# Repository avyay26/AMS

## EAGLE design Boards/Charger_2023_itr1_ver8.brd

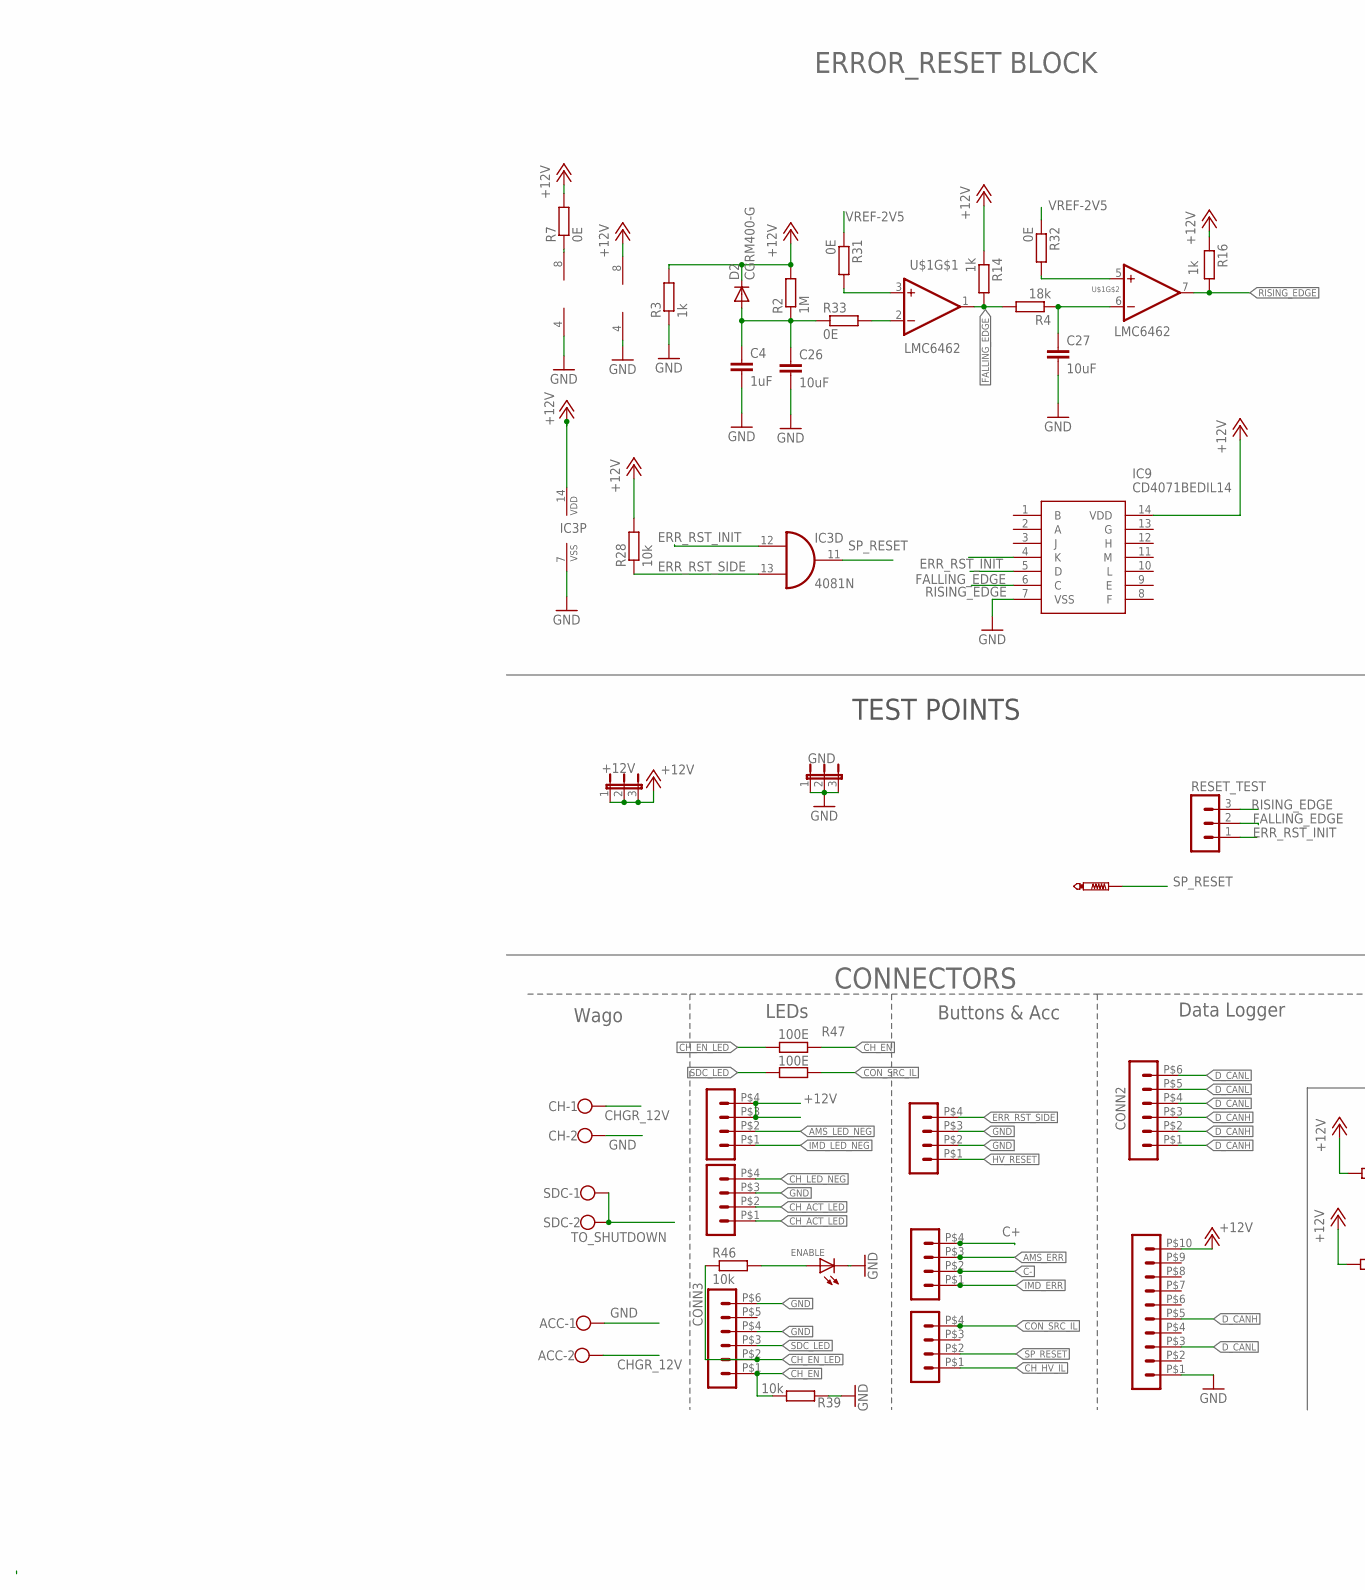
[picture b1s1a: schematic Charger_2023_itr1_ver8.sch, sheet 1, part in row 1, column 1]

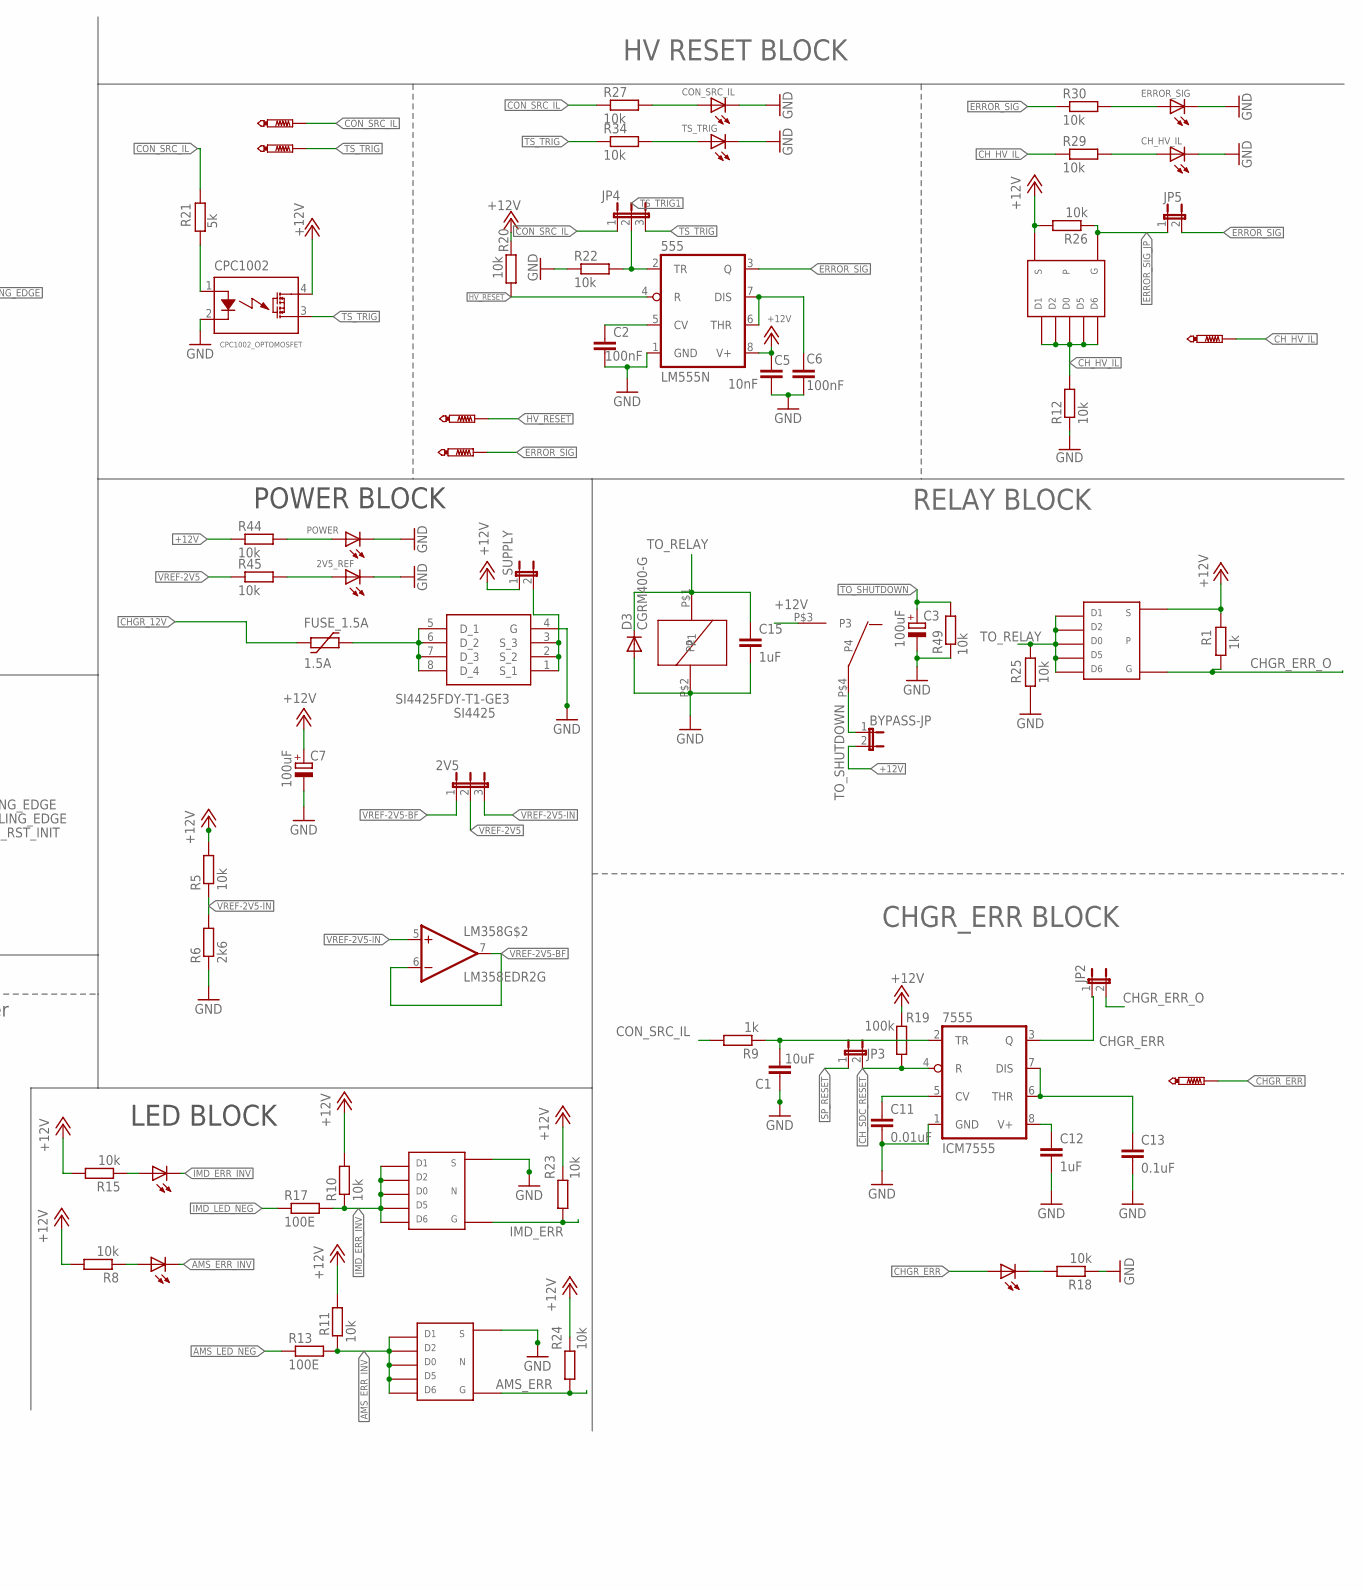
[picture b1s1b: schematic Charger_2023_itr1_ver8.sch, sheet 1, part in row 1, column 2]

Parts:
2V5: JP2E; JP2
2V5_REF: LED-FKIT-1206; FKIT-LED-1206
555: LM555N; DIL08
7555: ICM7555; DIL08
+12V: JP2E; JP2
ACC: W237-102
ACU, ACU1, ACU2, ACU3, ACU4: HEADER_POS4_43045-0412; 43045-0412
AMS: LED-FKIT-1206; FKIT-LED-1206
BYPASS-JP: JP1E; JP1
C1, C26, C27: 10uF; C0805
C2, C6: 100nF; C0805
C3, C7: 100uF; E2,5-6
C4, C12, C15: 1uF; C0805
C5: 10nF; C0805
C11: 0.01uF; C0805
C13: 0.1uF; C0805
CH: W237-102
CH-HV-IL: PTR1PAD1-13; P1-13
CHGR-ERR: PTR1PAD1-13; P1-13
CHGR_ERR: LED-FKIT-1206; FKIT-LED-1206
CH_HV_IL: LED-FKIT-1206; FKIT-LED-1206
CON-SRC-IL: PTR1PAD1-13; P1-13
CONN2, CONN3: HEADER_POS6_43045-0612; 43045-0612
CON_SRC_IL: LED-FKIT-1206; FKIT-LED-1206
CPC1002: CPC1002_OPTOMOSFET; SOP04
D2, D3: CGRM400-G; SOD-123_MINI-SMA
ENABLE: LED-FKIT-1206; FKIT-LED-1206
ERROR-SIG: PTR1PAD1-13; P1-13
ERROR_SIG: LED-FKIT-1206; FKIT-LED-1206
FUSE_1.5A: 1.5A; 1206L
GND: JP2E; JP2
HV-RESET: PTR1PAD1-13; P1-13
IC3: 4081N; DIL14
IC9: CD4071BEDIL14; DIL14
IMD: LED-FKIT-1206; FKIT-LED-1206
JP2, JP3, JP5: JP1E; JP1
JP4: JP2E; JP2
LM358: LM358EDR2G; SOIC-8
POWER: LED-FKIT-1206; FKIT-LED-1206
R1, R3, R9, R14, R16: 1k; R0805
R2: 1M; R0805
R4: 18k; R0805
R5, R8, R10, R11, R12, R15, R18, R20, R22, R23, R24, R25, R26, R27, R28, R29, R30, R34, R39, R44, R45, R46, R49: 10k; R0805
R6: 2k6; R0805
R7, R31, R32, R33: 0E; R0805
R13, R17: 100E; M0805
R19: 100k; R0805
R21: 5k; R0805
R47, R48: 100E; R0805
RESET_TEST: MA03-1
SDC: W237-102
SI4425: SI4425FDY-T1-GE3; SOIC127P600X175-8N
SP_RESET: PTR1PAD1-13; P1-13
SUPPLY: JP1E; JP1
TS-TRIG: PTR1PAD1-13; P1-13
TS_TRIG: LED-FKIT-1206; FKIT-LED-1206
U$1: LMC6462; S08
U$3, U$8: TSOP-6_PMOS
U$5, U$7: TSOP-6_NMOS
U$9: G6DN_RELAY
X5: HEADER_POS10_43045-1012; 43045-1012

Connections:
+12V: 555.8 (V+), 7555.8 (V+), +12V.1, +12V.2, +12V.3, ACU.P$3 (3), ACU.P$4 (4), BYPASS-JP.2, C5.1, C7.+, C12.1, CPC1002.4, D2.C, IC3.14 (VDD), IC9.14 (VDD), LM358.8 (V+), R1.2, R2.2, R3.2, R5.2, R7.2, R8.2, R10.2, R11.2, R14.1, R15.2, R16.1, R19.1, R20.2, R23.2, R24.2, R26.2, R28.2, R44.1, SUPPLY.1, U$3.S, U$8.S, U$9.P$3 (P3), X5.P$10 (10); also elsewhere on the board
AMS_ERR: ACU3.P$3 (3), R24.1, U$5.G
AMS_ERR_INV: AMS.C, R11.1, R13.2, U$5.1, U$5.2, U$5.5, U$5.6, U$5.D (D0)
AMS_LED_NEG: ACU.P$2 (2), R13.1
C+: ACU3.P$4 (4); also elsewhere on the board
C-: ACU3.P$2 (2); also elsewhere on the board
CHGR_12V: ACC.2, CH.1, FUSE_1.5A.P$1 (1)
CHGR_ERR: 7555.3 (Q), CHGR-ERR.TP, CHGR_ERR.A, JP2.1
CHGR_ERR_O: JP2.2, R1.1, U$3.G
CH_ACT_LED: ACU2.P$1 (1), ACU2.P$2 (2); also elsewhere on the board
CH_EN: CONN3.P$1 (1), R39.2, R47.2
CH_EN_LED: CONN3.P$2 (2), R46.1, R47.1
CH_HV_IL: ACU4.P$1 (1), CH-HV-IL.TP, R12.2, R29.1, U$8.1, U$8.2, U$8.5, U$8.6, U$8.D (D0)
CH_LED_NEG: ACU2.P$4 (4); also elsewhere on the board
CH_SDC_RESET: 7555.4 (R), JP3.2, R19.2
CON_SRC_IL: ACU4.P$4 (4), CON-SRC-IL.TP, JP4.1, R9.2, R21.2, R27.1, R48.2
D_CANH: CONN2.P$1 (1), CONN2.P$2 (2), CONN2.P$3 (3), X5.P$5 (5)
D_CANL: CONN2.P$4 (4), CONN2.P$5 (5), CONN2.P$6 (6), X5.P$3 (3)
ERROR_SIG: 555.3 (Q), ERROR-SIG.TP, JP5.2, R30.1
ERROR_SIG_JP: JP5.1, R26.1, U$8.G
ERR_RST_INIT: IC3.12 (I0), IC9.4 (K), RESET_TEST.1
ERR_RST_SIDE: ACU1.P$4 (4), IC3.13 (I1), R28.1
FALLING_EDGE: IC9.5 (D), R4.2, R14.2, RESET_TEST.2, U$1.1 (OUT)
GND: 2V5_REF.C, 555.1 (GND), 7555.1 (GND), ACC.1, ACU1.P$2 (2), ACU1.P$3 (3), ACU2.P$3 (3), C1.1, C2.2, C3.-, C4.2, C5.2, C6.2, C7.-, C11.2, C12.2, C13.2, C15.2, C26.2, C27.2, CH.2, CH_HV_IL.C, CONN3.P$4 (4), CONN3.P$6 (6), CON_SRC_IL.C, CPC1002.2, D3.A, ENABLE.C, ERROR_SIG.C, GND.1, GND.2, GND.3, IC3.7 (VSS), IC9.7 (VSS), LM358.4 (V-), POWER.C, R3.1, R6.1, R12.1, R18.1, R22.1, R25.1, R39.1, R49.1, SI4425.4 (G), TS_TRIG.C, U$1.4 (V-), U$5.S, U$7.S, U$9.P$2 (P2), X5.P$1 (1); also elsewhere on the board
HV_RESET: 555.4 (R), ACU1.P$1 (1), HV-RESET.TP, R20.1
IMD_ERR: ACU3.P$1 (1), R23.1, U$7.G
IMD_ERR_INV: IMD.C, R10.1, R17.2, U$7.1, U$7.2, U$7.5, U$7.6, U$7.D (D0)
IMD_LED_NEG: ACU.P$1 (1), R17.1
unnamed: 7555.2 (TR), C1.2, R9.1
unnamed: IMD.A, R15.1
unnamed: 555.5 (CV), C2.1
unnamed: CHGR_ERR.C, R18.2
unnamed: R7.1, U$1.8 (V+)
unnamed: C4.1, C26.1, D2.A, R2.1, R33.1
unnamed: 555.6 (THR), 555.7 (DIS), C6.1
unnamed: AMS.A, R8.1
unnamed: CPC1002.1, R21.1
unnamed: CON_SRC_IL.A, R27.2
unnamed: CH_HV_IL.A, R29.2
unnamed: C27.1, R4.1, U$1.6 (-IN)
unnamed: ERROR_SIG.A, R30.2
unnamed: R34.2, TS_TRIG.A
unnamed: 7555.5 (CV), C11.1
unnamed: 7555.6 (THR), 7555.7 (DIS), C13.1
unnamed: SI4425.1 (S_1), SI4425.2 (S_2), SI4425.3 (S_3), SUPPLY.2
unnamed: FUSE_1.5A.P$2 (2), SI4425.5 (D_1), SI4425.6 (D_2), SI4425.7 (D_3), SI4425.8 (D_4)
unnamed: POWER.A, R44.2
unnamed: 2V5_REF.A, R45.2
unnamed: ENABLE.A, R46.2
unnamed: R31.2, U$1.3 (+IN)
unnamed: R32.2, U$1.5 (+IN)
unnamed: R33.2, U$1.2 (-IN)
RISING_EDGE: IC9.6 (C), R16.2, RESET_TEST.3, U$1.7 (OUT)
SDC_LED: CONN3.P$3 (3), R48.1
SP_RESET: ACU4.P$2 (2), IC3.11 (O), JP3.1, SP_RESET.TP
TO_RELAY: C15.1, D3.C, R25.2, U$3.1, U$3.2, U$3.5, U$3.6, U$3.D (D0), U$9.P$1 (P1)
TO_SHUTDOWN: BYPASS-JP.1, C3.+, R49.2, SDC.1, SDC.2, U$9.P$4 (P4)
TS_TRIG: CPC1002.3, JP4.3, R34.1, TS-TRIG.TP
TS_TRIG1: 555.2 (TR), JP4.2, R22.2
VREF-2V5: 2V5.2, R31.1, R32.1, R45.1
VREF-2V5-BF: 2V5.1, LM358.6 (-IN), LM358.7 (OUT)
VREF-2V5-IN: 2V5.3, LM358.5 (+IN), R5.1, R6.2

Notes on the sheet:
CHGR_ERR BLOCK
ERROR_RESET BLOCK
RELAY BLOCK
CONNECTORS
POWER BLOCK
TEST POINTS
LED BLOCK
HV RESET BLOCK
Wago
LEDs
Buttons & Acc
Data Logger

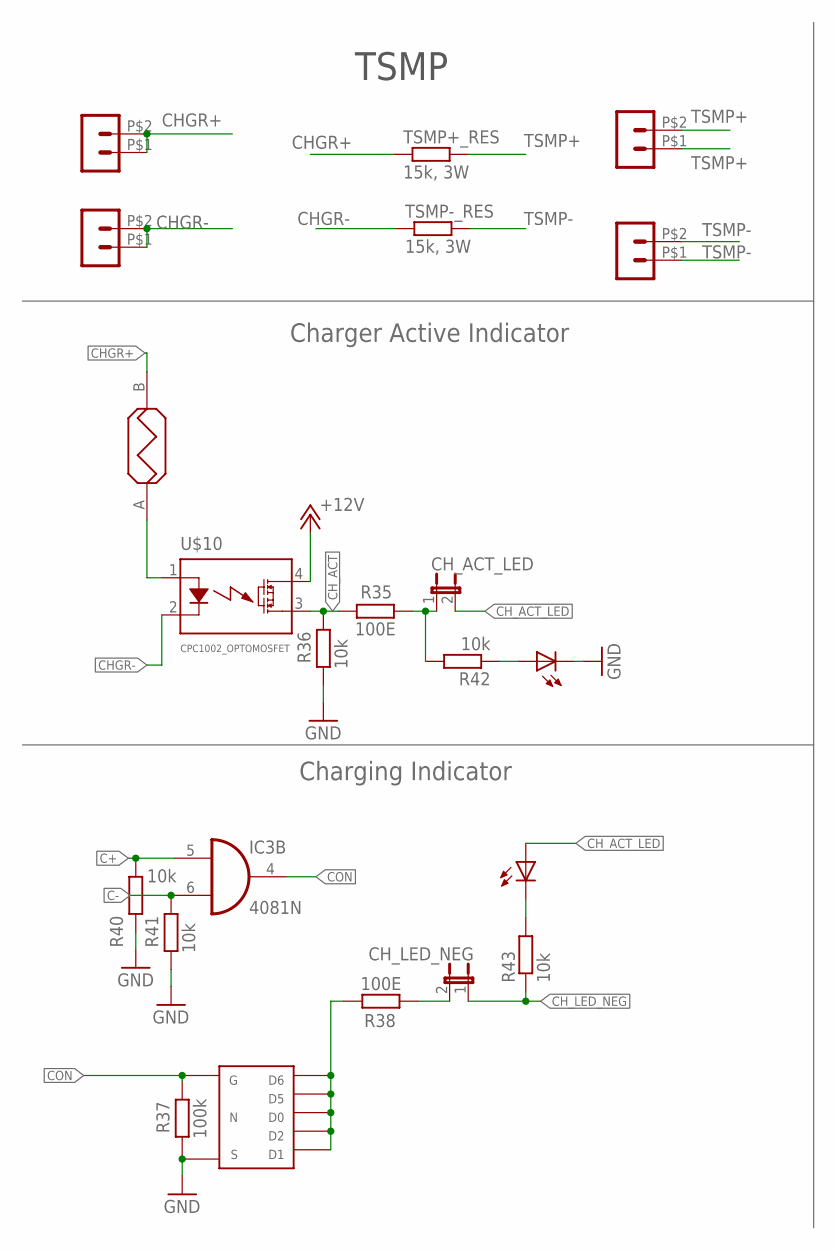
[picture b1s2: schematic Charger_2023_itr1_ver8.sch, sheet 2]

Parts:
CHARGING: LED-FKIT-1206; FKIT-LED-1206
CH_ACT: LED-FKIT-1206; FKIT-LED-1206
CH_ACT_LED: JP1E; JP1
CH_LED_NEG: JP1E; JP1
IC3: 4081N; DIL14
LV_ECU, LV_ECU1, LV_ECU2, LV_ECU3: HEADER_POS2_43045-0212; 43045-0212
R35, R38: 100E; M0805
R36, R40, R41: 10k; M0805
R37: 100k; M0805
R42, R43: 10k; R0805
TSMP+_RES: 15k, 3W; P0613/15
TSMP-_RES: 15k, 3W; P0613/15
U$2_100K10W2: POWER_RESISTOR
U$10: CPC1002_OPTOMOSFET; SOP04
U$12: TSOP-6_NMOS

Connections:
+12V: U$10.4; also elsewhere on the board
C+: IC3.5 (I0), R40.2; also elsewhere on the board
C-: IC3.6 (I1), R41.2; also elsewhere on the board
CHGR+: LV_ECU2.P$1 (1), LV_ECU2.P$2 (2), TSMP+_RES.1, U$2_100K10W2.B
CHGR-: LV_ECU3.P$1 (1), LV_ECU3.P$2 (2), TSMP-_RES.1, U$10.2
CH_ACT: R35.1, R36.2, U$10.3
CH_ACT_LED: CHARGING.A, CH_ACT_LED.2; also elsewhere on the board
CH_LED_NEG: CH_LED_NEG.1, R43.1; also elsewhere on the board
CON: IC3.4 (O), R37.2, U$12.G
GND: CH_ACT.C, R36.1, R37.1, R40.1, R41.1, U$12.S; also elsewhere on the board
unnamed: CH_ACT.A, R42.1
unnamed: R38.2, U$12.1, U$12.2, U$12.5, U$12.6, U$12.D (D0)
unnamed: CH_LED_NEG.2, R38.1
unnamed: CH_ACT_LED.1, R35.2, R42.2
unnamed: U$2_100K10W2.A, U$10.1
unnamed: CHARGING.C, R43.2
TSMP+: LV_ECU.P$1 (1), LV_ECU.P$2 (2), TSMP+_RES.2
TSMP-: LV_ECU1.P$1 (1), LV_ECU1.P$2 (2), TSMP-_RES.2

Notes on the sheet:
TSMP
Charger Active Indicator
Charging Indicator

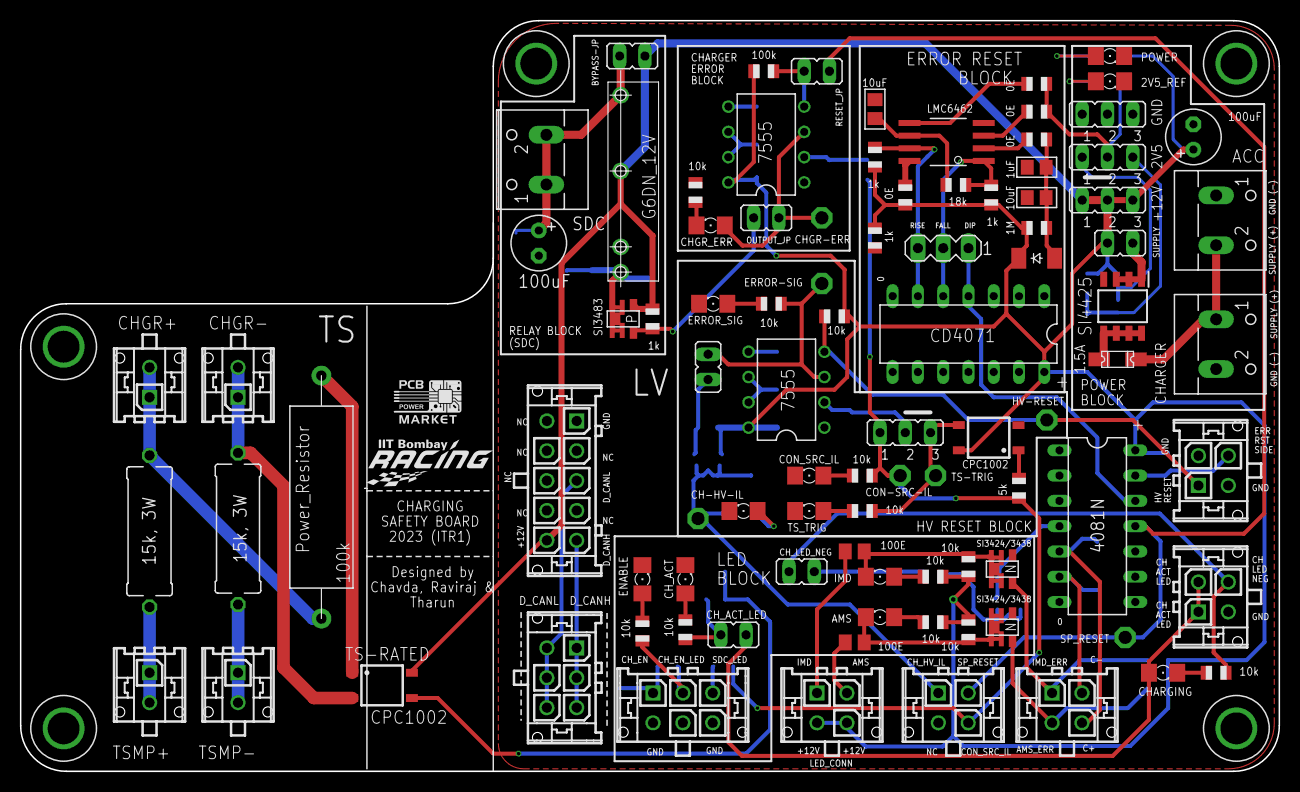
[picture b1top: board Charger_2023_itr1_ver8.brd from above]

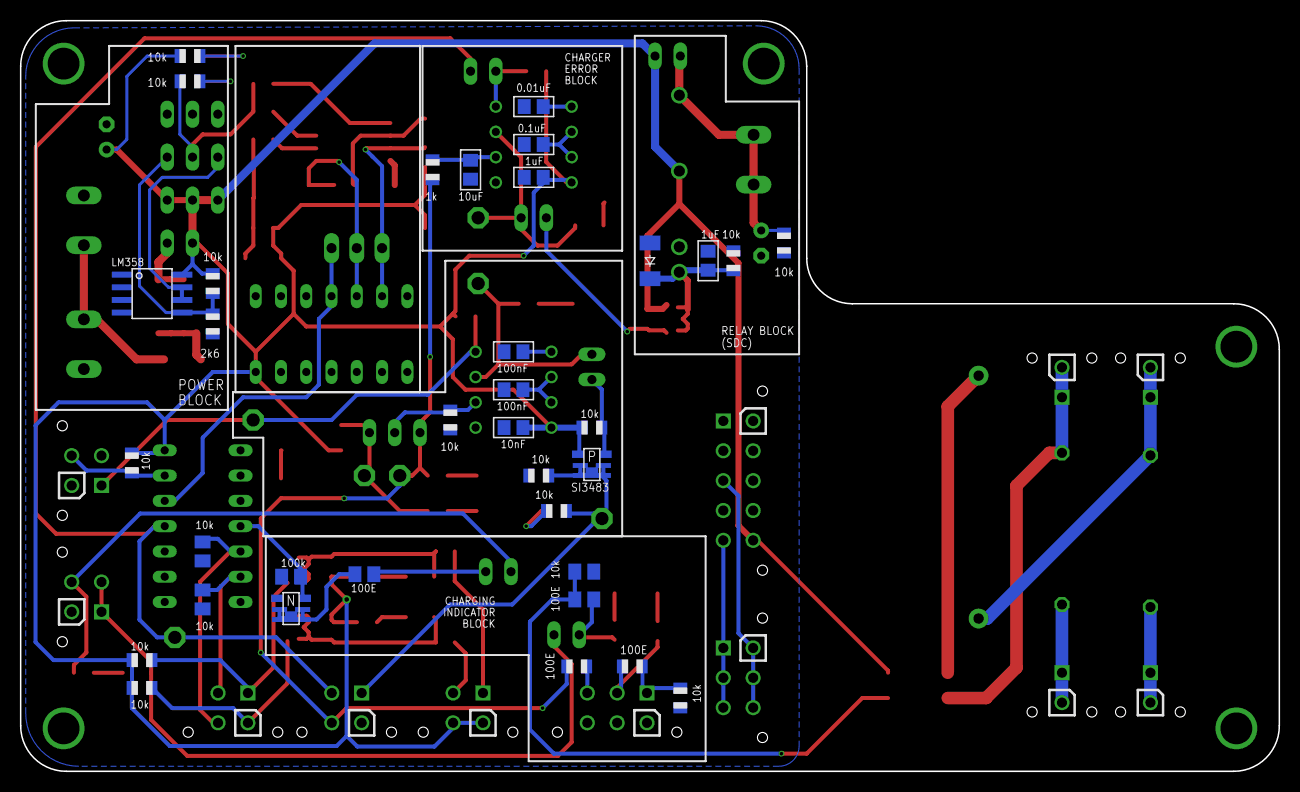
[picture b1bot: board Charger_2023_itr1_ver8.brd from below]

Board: 2 copper layers, 126.5 x 75.4 mm, 131 parts (35 on the bottom side), 74 nets.

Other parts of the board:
U$2: LOGO_PCBPOWER; 270X170
U$4: RACING_LOGO_190MIL

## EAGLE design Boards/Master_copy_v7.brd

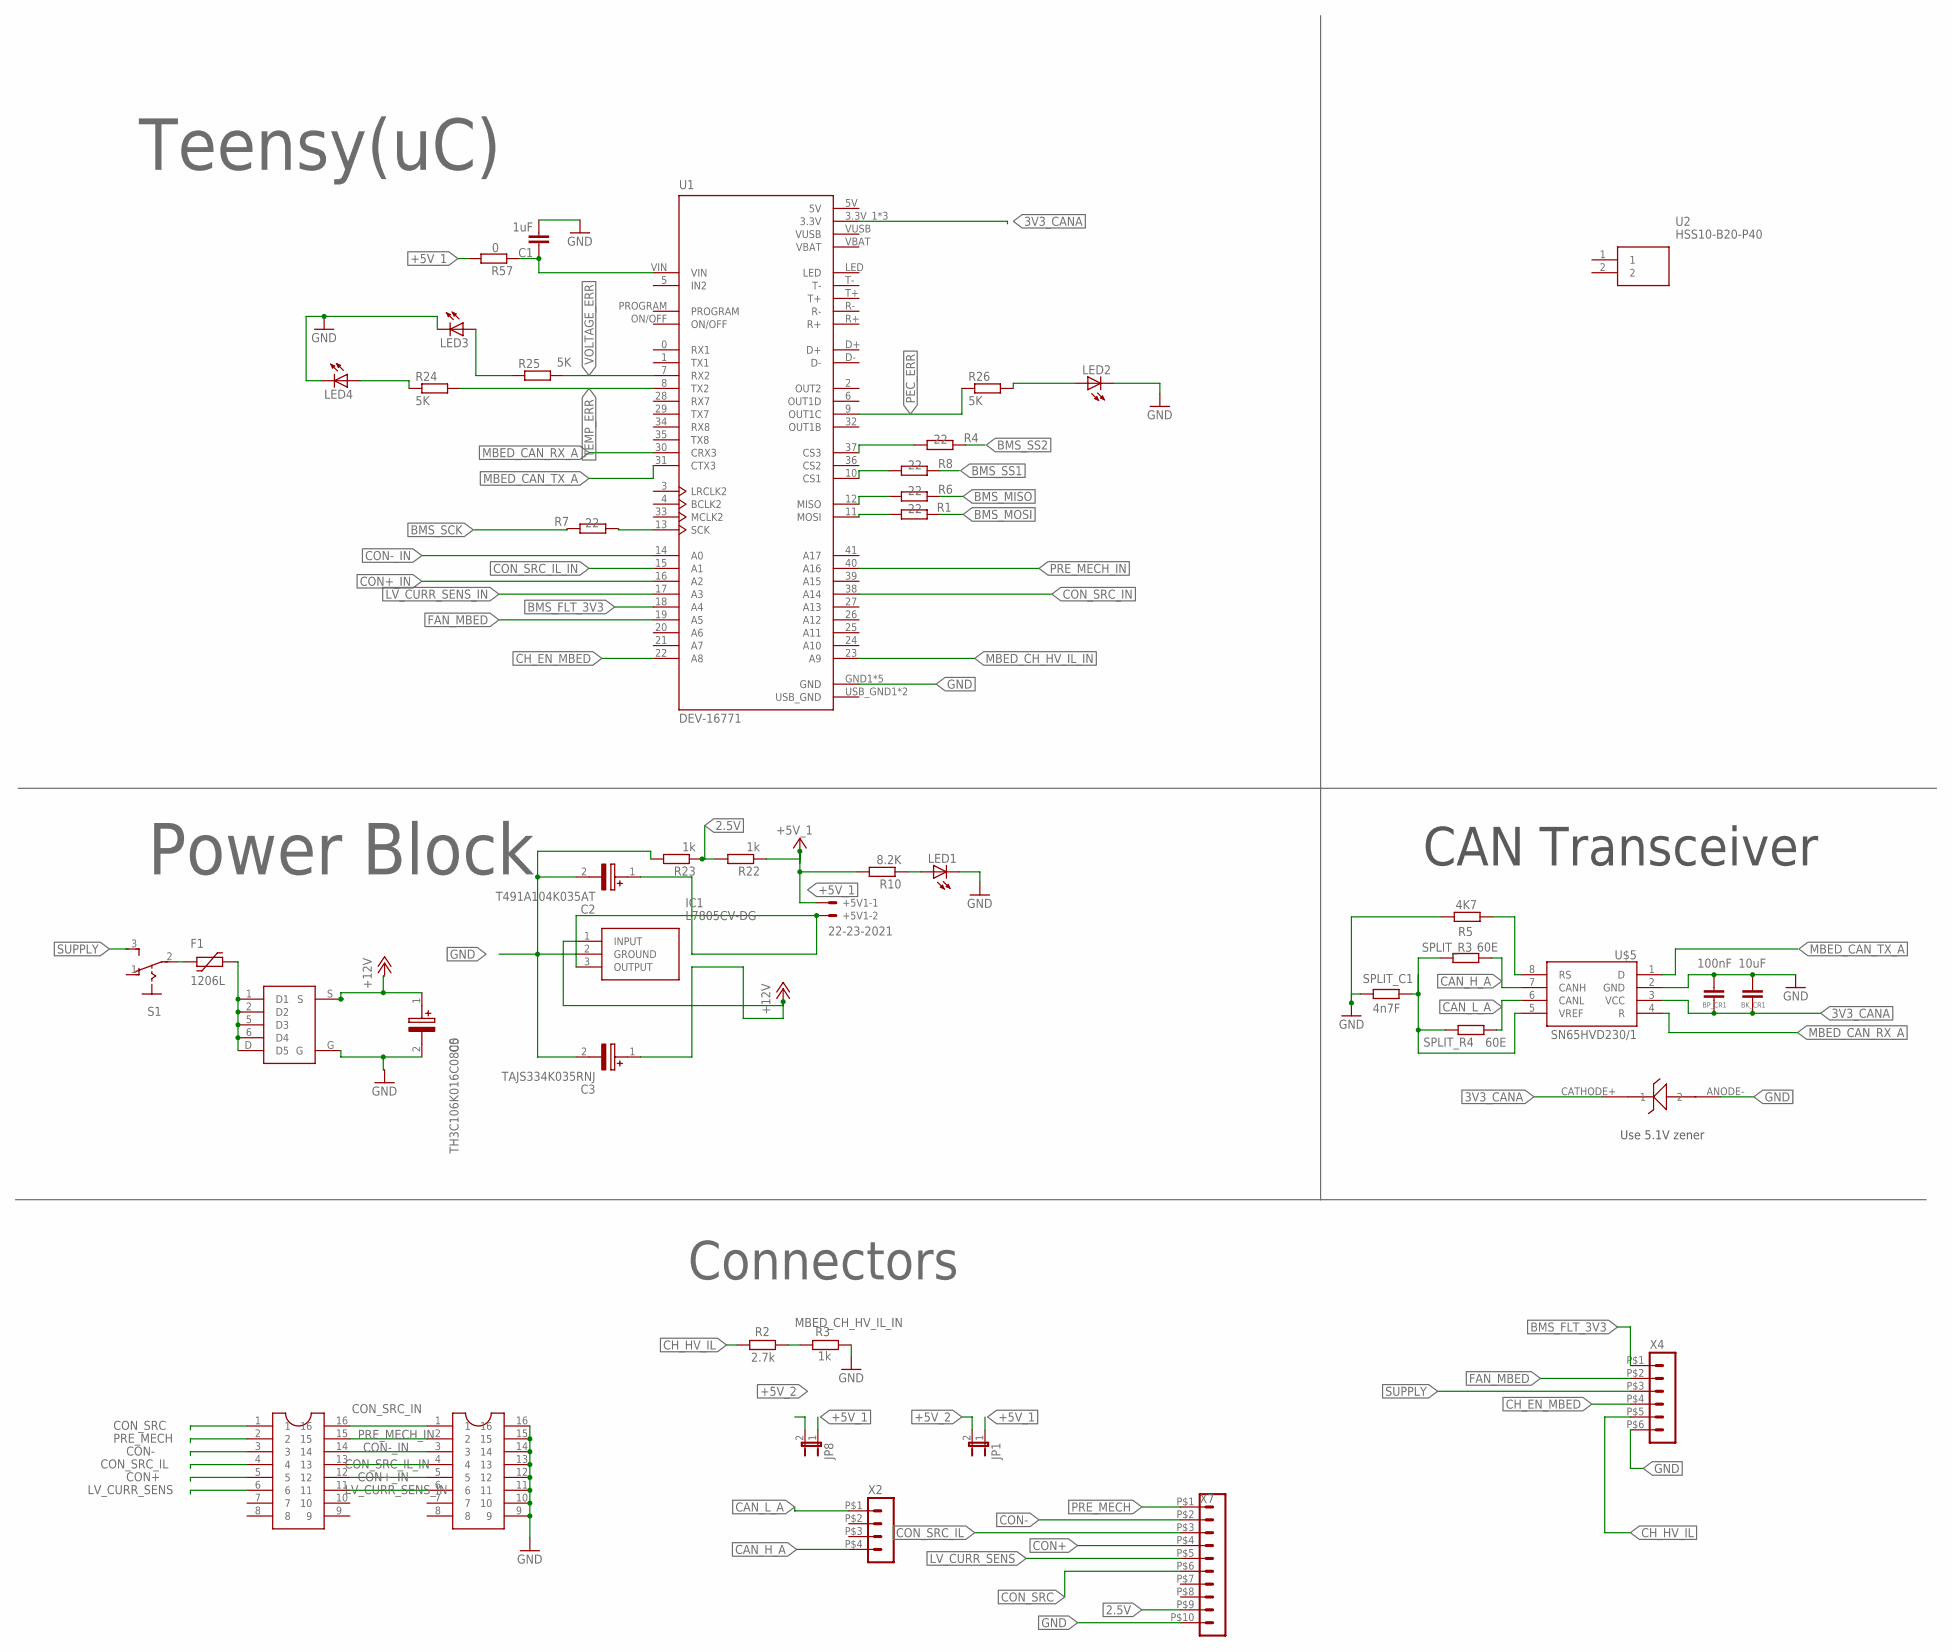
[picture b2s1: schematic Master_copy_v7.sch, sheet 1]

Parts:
+5V1: 22-23-2021
BK_CR1: 10uF; C0805
BP_CR1: 100nF; C0805
C1: 1uF; C0805K
C2: T491A104K035AT; T491A
C3: TAJS334K035RNJ; CAPPM3216X120N
C5: TH3C106K016C0800; CAPPM6032X280N
F1: 1206L
IC1: L7805CV-DG; TO255P460X1020X2008-3P
JP1, JP8: JP1E; JP1
LED1, LED2, LED3, LED4: LED; CHIP-LED0805
R1, R4, R6, R7, R8: 22; R0805
R2: 2.7k; R0805
R3, R22, R23: 1k; R0805
R5: 4K7; R0805
R10: 8.2K; R0805
R24, R25, R26: 5K; R0805
R57: 0; R0805
RESISTOR_NET_2.7K: REESISTOR_NET_16; RESISTOR_NET_16
S1: STS121PC04
S4: DMP3125L/SQ3419AEEV
SPLIT_C1: 4n7F; R0805
SPLIT_R3, SPLIT_R4: 60E; R0805
U1: DEV-16771; MODULE_DEV-16771
U2: HSS10-B20-P40; HSS10B20P40
U$5: SN65HVD230/1; SO8
U$8: ZENER_DIODE; SOD323HE
U$19: REESISTOR_NET_16; RESISTOR_NET_16
X2: CON-MOLEX-MICRO-FIT-3_0_HEADER_POS4_43045-0412; CON-MOLEX-MICRO-FIT-3_0_43045-0412
X4: HEADER_POS6_43045-0612; 43045-0612
X7: HEADER_POS10_43045-1012; 43045-1012

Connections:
2.5V: R22.2, R23.1, X7.P$9 (9)
3V3_CANA: BK_CR1.1, BP_CR1.1, U1.3.3V_1 (3.3V), U1.3.3V_2 (3.3V), U1.3.3V_3 (3.3V), U$5.3 (VCC), U$8.CATHODE+ (1)
5V: U1.5V
+5V_1: +5V1.1, JP1.1, JP8.1, R10.2, R22.1, R57.2
+5V_2: JP1.2, JP8.2; also elsewhere on the board
+12V: C3.1 (+), C5.1 (+), IC1.1 (INPUT), S4.S
BMS_FLT_3V3: U1.18 (A4), X4.P$1 (1)
BMS_MISO: R6.1; also elsewhere on the board
BMS_MOSI: R1.1; also elsewhere on the board
BMS_SCK: R7.1; also elsewhere on the board
BMS_SS1: R8.1; also elsewhere on the board
BMS_SS2: R4.1; also elsewhere on the board
CAN_H_A: SPLIT_R3.1, U$5.7 (CANH), X2.P$4 (4)
CAN_L_A: SPLIT_R4.1, U$5.6 (CANL), X2.P$1 (1)
CH_EN_MBED: U1.22 (A8), X4.P$4 (4)
CH_HV_IL: R2.1, X4.P$5 (5)
CON+: RESISTOR_NET_2.7K.5, X7.P$4 (4)
CON+_IN: RESISTOR_NET_2.7K.12, U1.16 (A2), U$19.5
CON-: RESISTOR_NET_2.7K.3, X7.P$2 (2)
CON-_IN: RESISTOR_NET_2.7K.14, U1.14 (A0), U$19.3
CON_SRC: RESISTOR_NET_2.7K.1, X7.P$6 (6)
CON_SRC_IL: RESISTOR_NET_2.7K.4, X7.P$3 (3)
CON_SRC_IL_IN: RESISTOR_NET_2.7K.13, U1.15 (A1), U$19.4
CON_SRC_IN: RESISTOR_NET_2.7K.16, U1.38 (A14), U$19.1
FAN_MBED: U1.19 (A5), X4.P$2 (2)
GND: BK_CR1.2, BP_CR1.2, C1.2, C2.2 (-), C3.2 (-), C5.2 (-), IC1.2 (GROUND), LED1.C, LED2.C, LED3.C, LED4.C, R3.2, R5.1, R23.2, S4.G, SPLIT_C1.2, U1.GND1 (GND), U1.GND2 (GND), U1.GND3 (GND), U1.GND4 (GND), U1.GND5 (GND), U$5.2 (GND), U$8.ANODE- (2), U$19.9, U$19.10, U$19.11, U$19.12, U$19.13, U$19.14, U$19.15, U$19.16, X4.P$6 (6), X7.P$10 (10); also elsewhere on the board
LV_CURR_SENS: RESISTOR_NET_2.7K.6, X7.P$5 (5)
LV_CURR_SENS_IN: RESISTOR_NET_2.7K.11, U1.17 (A3), U$19.6
MBED_CAN_RX_A: U1.30 (CRX3), U$5.4 (R)
MBED_CAN_TX_A: U1.31 (CTX3), U$5.1 (D)
MBED_CH_HV_IL_IN: R2.2, R3.1, U1.23 (A9)
unnamed: R4.2, U1.37 (CS3)
unnamed: F1.P$1 (1), S1.2
unnamed: R5.2, U$5.8 (RS)
unnamed: R1.2, U1.11 (MOSI)
unnamed: R6.2, U1.12 (MISO)
unnamed: R8.2, U1.10 (CS1)
unnamed: R7.2, U1.13 (SCK)
unnamed: +5V1.2, C2.1 (+), IC1.3 (OUTPUT)
unnamed: LED1.A, R10.1
unnamed: LED3.A, R25.1
unnamed: LED4.A, R24.1
unnamed: LED2.A, R26.2
unnamed: SPLIT_C1.1, SPLIT_R3.2, SPLIT_R4.2, U$5.5 (VREF)
unnamed: F1.P$2 (2), S4.1 (D1), S4.2 (D2), S4.5 (D3), S4.6 (D4), S4.D (D5)
unnamed: C1.1, R57.1, U1.VIN
PEC_ERR: R26.1, U1.9 (OUT1C)
PRE_MECH: RESISTOR_NET_2.7K.2, X7.P$1 (1)
PRE_MECH_IN: RESISTOR_NET_2.7K.15, U1.40 (A16), U$19.2
SUPPLY: S1.3 (S), X4.P$3 (3)
TEMP_ERR: R24.2, U1.8 (TX2)
USB_GND: U1.USB_GND1 (USB_GND), U1.USB_GND2 (USB_GND)
VOLTAGE_ERR: R25.2, U1.7 (RX2)

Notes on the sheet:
CAN Transceiver
Power Block
Use 5.1V zener
Connectors
Teensy(uC)

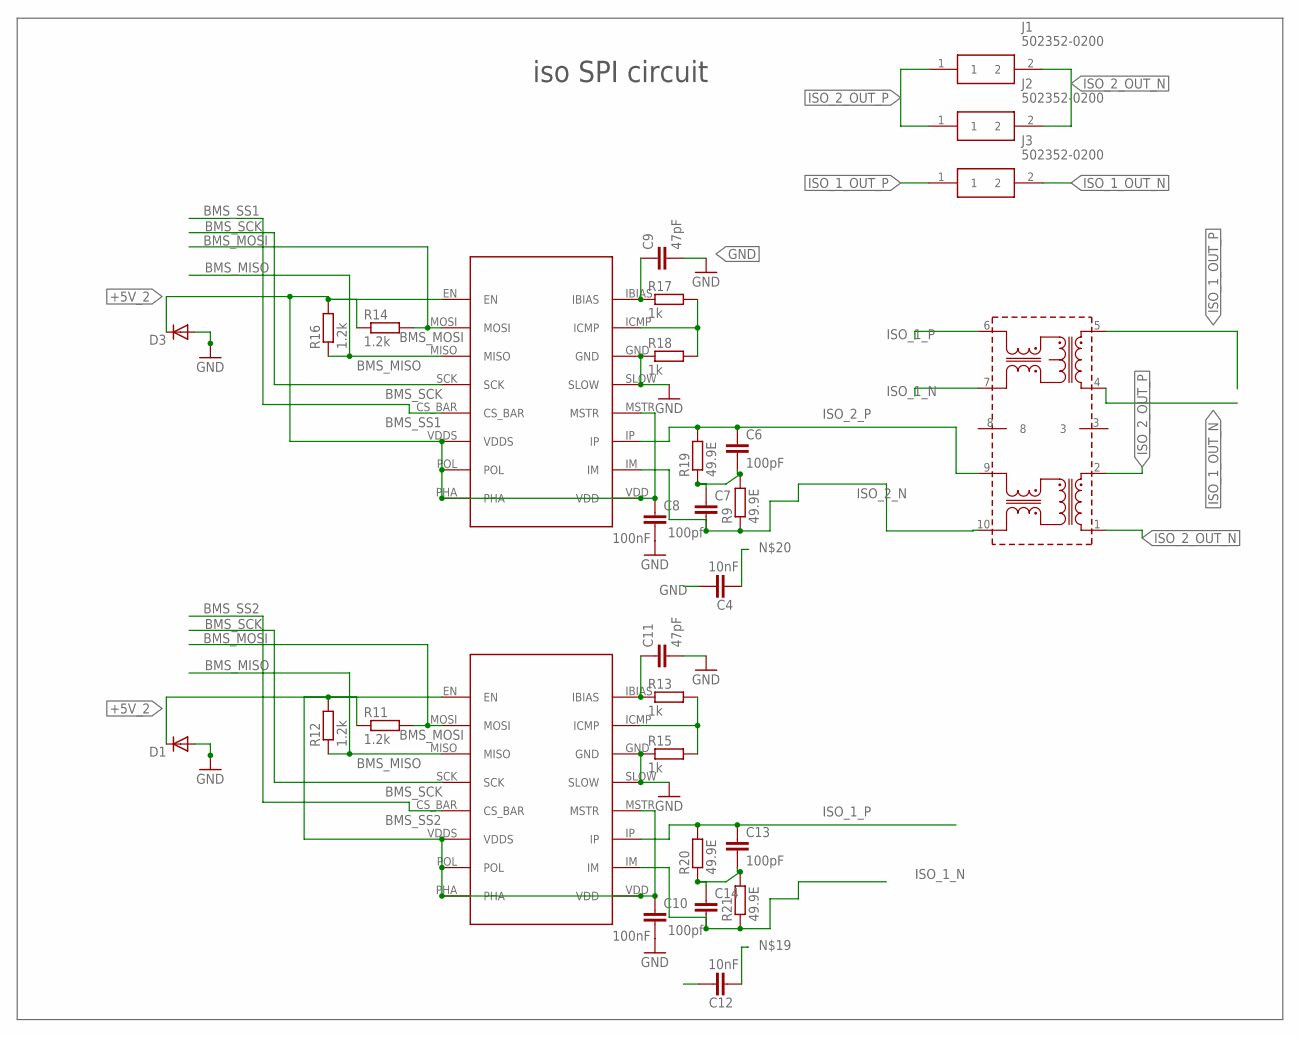
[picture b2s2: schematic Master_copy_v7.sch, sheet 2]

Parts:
C4, C12: 10nF; C0805
C6, C13: 100pF; C0603
C7, C14: 100pf; C0603
C8, C10: 100nF; C0805
C9, C11: 47pF; C0805
D1, D3: DIODE-SOD123; SOD123
J1, J2, J3: 502352-0200; 5023520200
R9, R19, R20, R21: 49.9E; R0805
R11, R12, R14, R16: 1.2k; R0805
R13, R15, R17, R18: 1k; R0805
U$1, U$4: LTC6820; 16-PINMSOP
U$2: HM2100NL

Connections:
+5V_2: C8.1, C10.1, D1.C, D3.C, R11.1, R12.2, R14.1, R16.2, U$1.EN, U$1.MSTR, U$1.PHA, U$1.POL, U$1.VDD, U$1.VDDS, U$4.EN, U$4.MSTR, U$4.PHA, U$4.POL, U$4.VDD, U$4.VDDS; also elsewhere on the board
BMS_MISO: R12.1, R16.1, U$1.MISO, U$4.MISO; also elsewhere on the board
BMS_MOSI: R11.2, R14.2, U$1.MOSI, U$4.MOSI; also elsewhere on the board
BMS_SCK: U$1.SCK, U$4.SCK; also elsewhere on the board
BMS_SS1: U$1.CS_BAR; also elsewhere on the board
BMS_SS2: U$4.CS_BAR; also elsewhere on the board
GND: C4.1, C8.2, C9.2, C10.2, C11.2, C12.1, D1.A, D3.A, R15.1, R18.1, U$1.GND, U$1.SLOW, U$4.GND, U$4.SLOW; also elsewhere on the board
ISO_1_N: C14.2, R21.1, U$2.7, U$4.IM
ISO_1_OUT_N: J3.2, U$2.4
ISO_1_OUT_P: J3.1, U$2.5
ISO_1_P: C13.1, R20.2, U$2.6, U$4.IP
ISO_2_N: C7.2, R9.1, U$1.IM, U$2.10
ISO_2_OUT_N: J1.2, J2.2, U$2.1
ISO_2_OUT_P: J1.1, J2.1, U$2.2
ISO_2_P: C6.1, R19.2, U$1.IP, U$2.9
unnamed: R17.2, R18.2, U$1.ICMP
unnamed: C9.1, R17.1, U$1.IBIAS
unnamed: R13.2, R15.2, U$4.ICMP
unnamed: C11.1, R13.1, U$4.IBIAS
unnamed: C12.2, C13.2, C14.1, R20.1, R21.2
unnamed: C4.2, C6.2, C7.1, R9.2, R19.1

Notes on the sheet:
iso SPI circuit

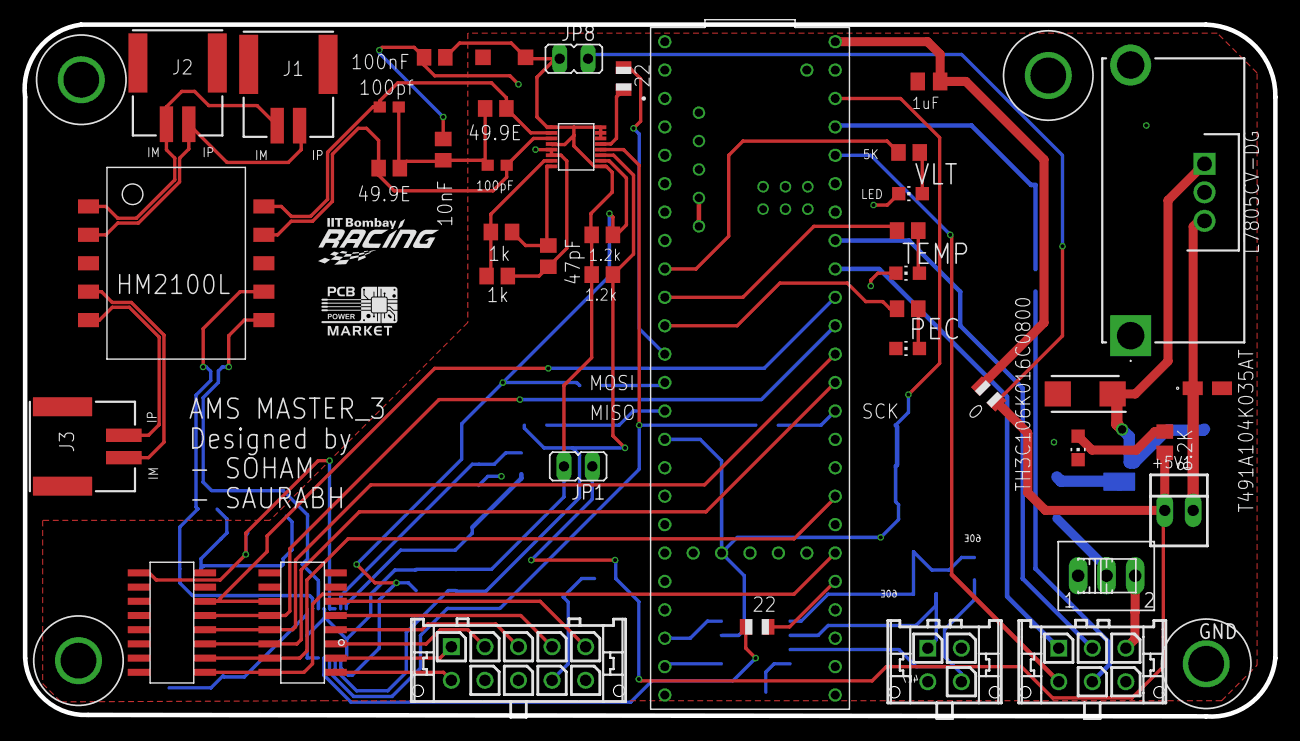
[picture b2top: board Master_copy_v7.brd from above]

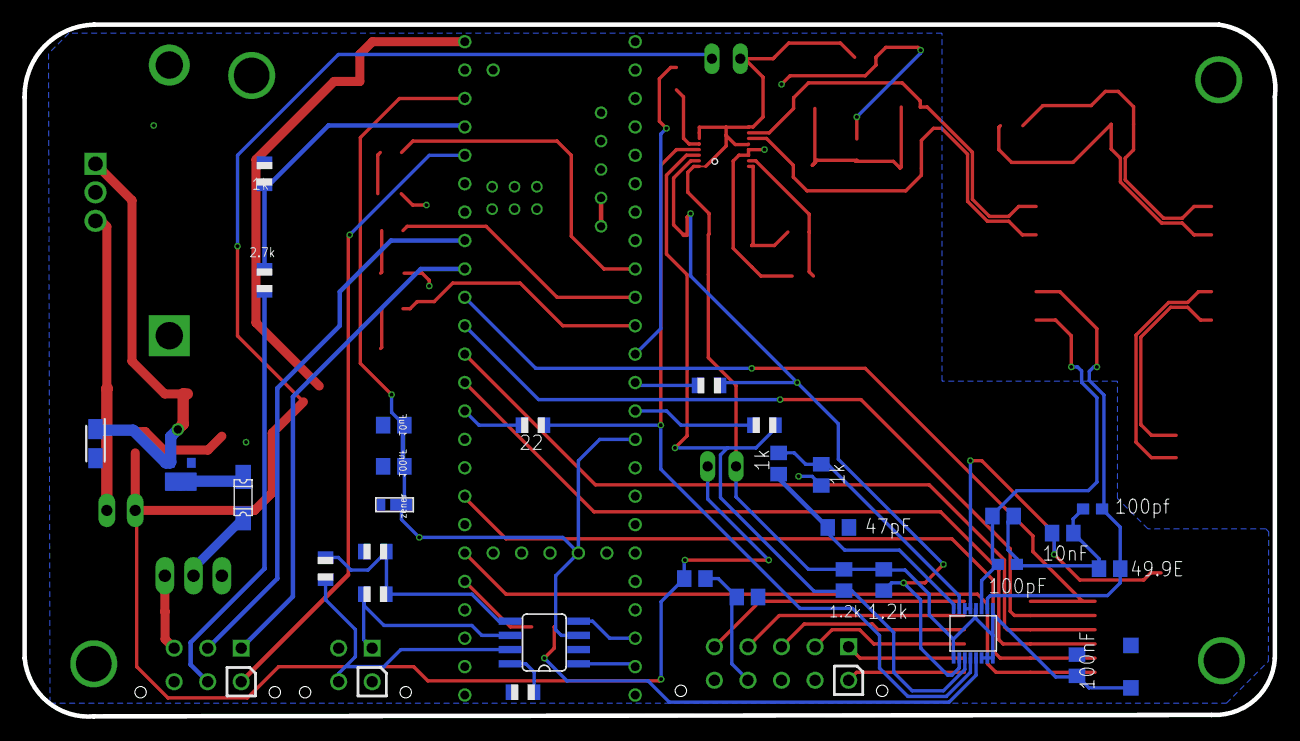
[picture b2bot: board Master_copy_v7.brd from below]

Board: 2 copper layers, 111.8 x 61.9 mm, 76 parts (31 on the bottom side), 66 nets.

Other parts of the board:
U$3: IITBR_LOGO
U$7: LOGO_PCBPOWER; 270X170

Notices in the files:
parts and their libraries:
SparkFun-Aesthetics: Licensing: Creative Commons ShareAlike 4.0 International - https://creativecommons.org/licenses/by-sa/4.0
